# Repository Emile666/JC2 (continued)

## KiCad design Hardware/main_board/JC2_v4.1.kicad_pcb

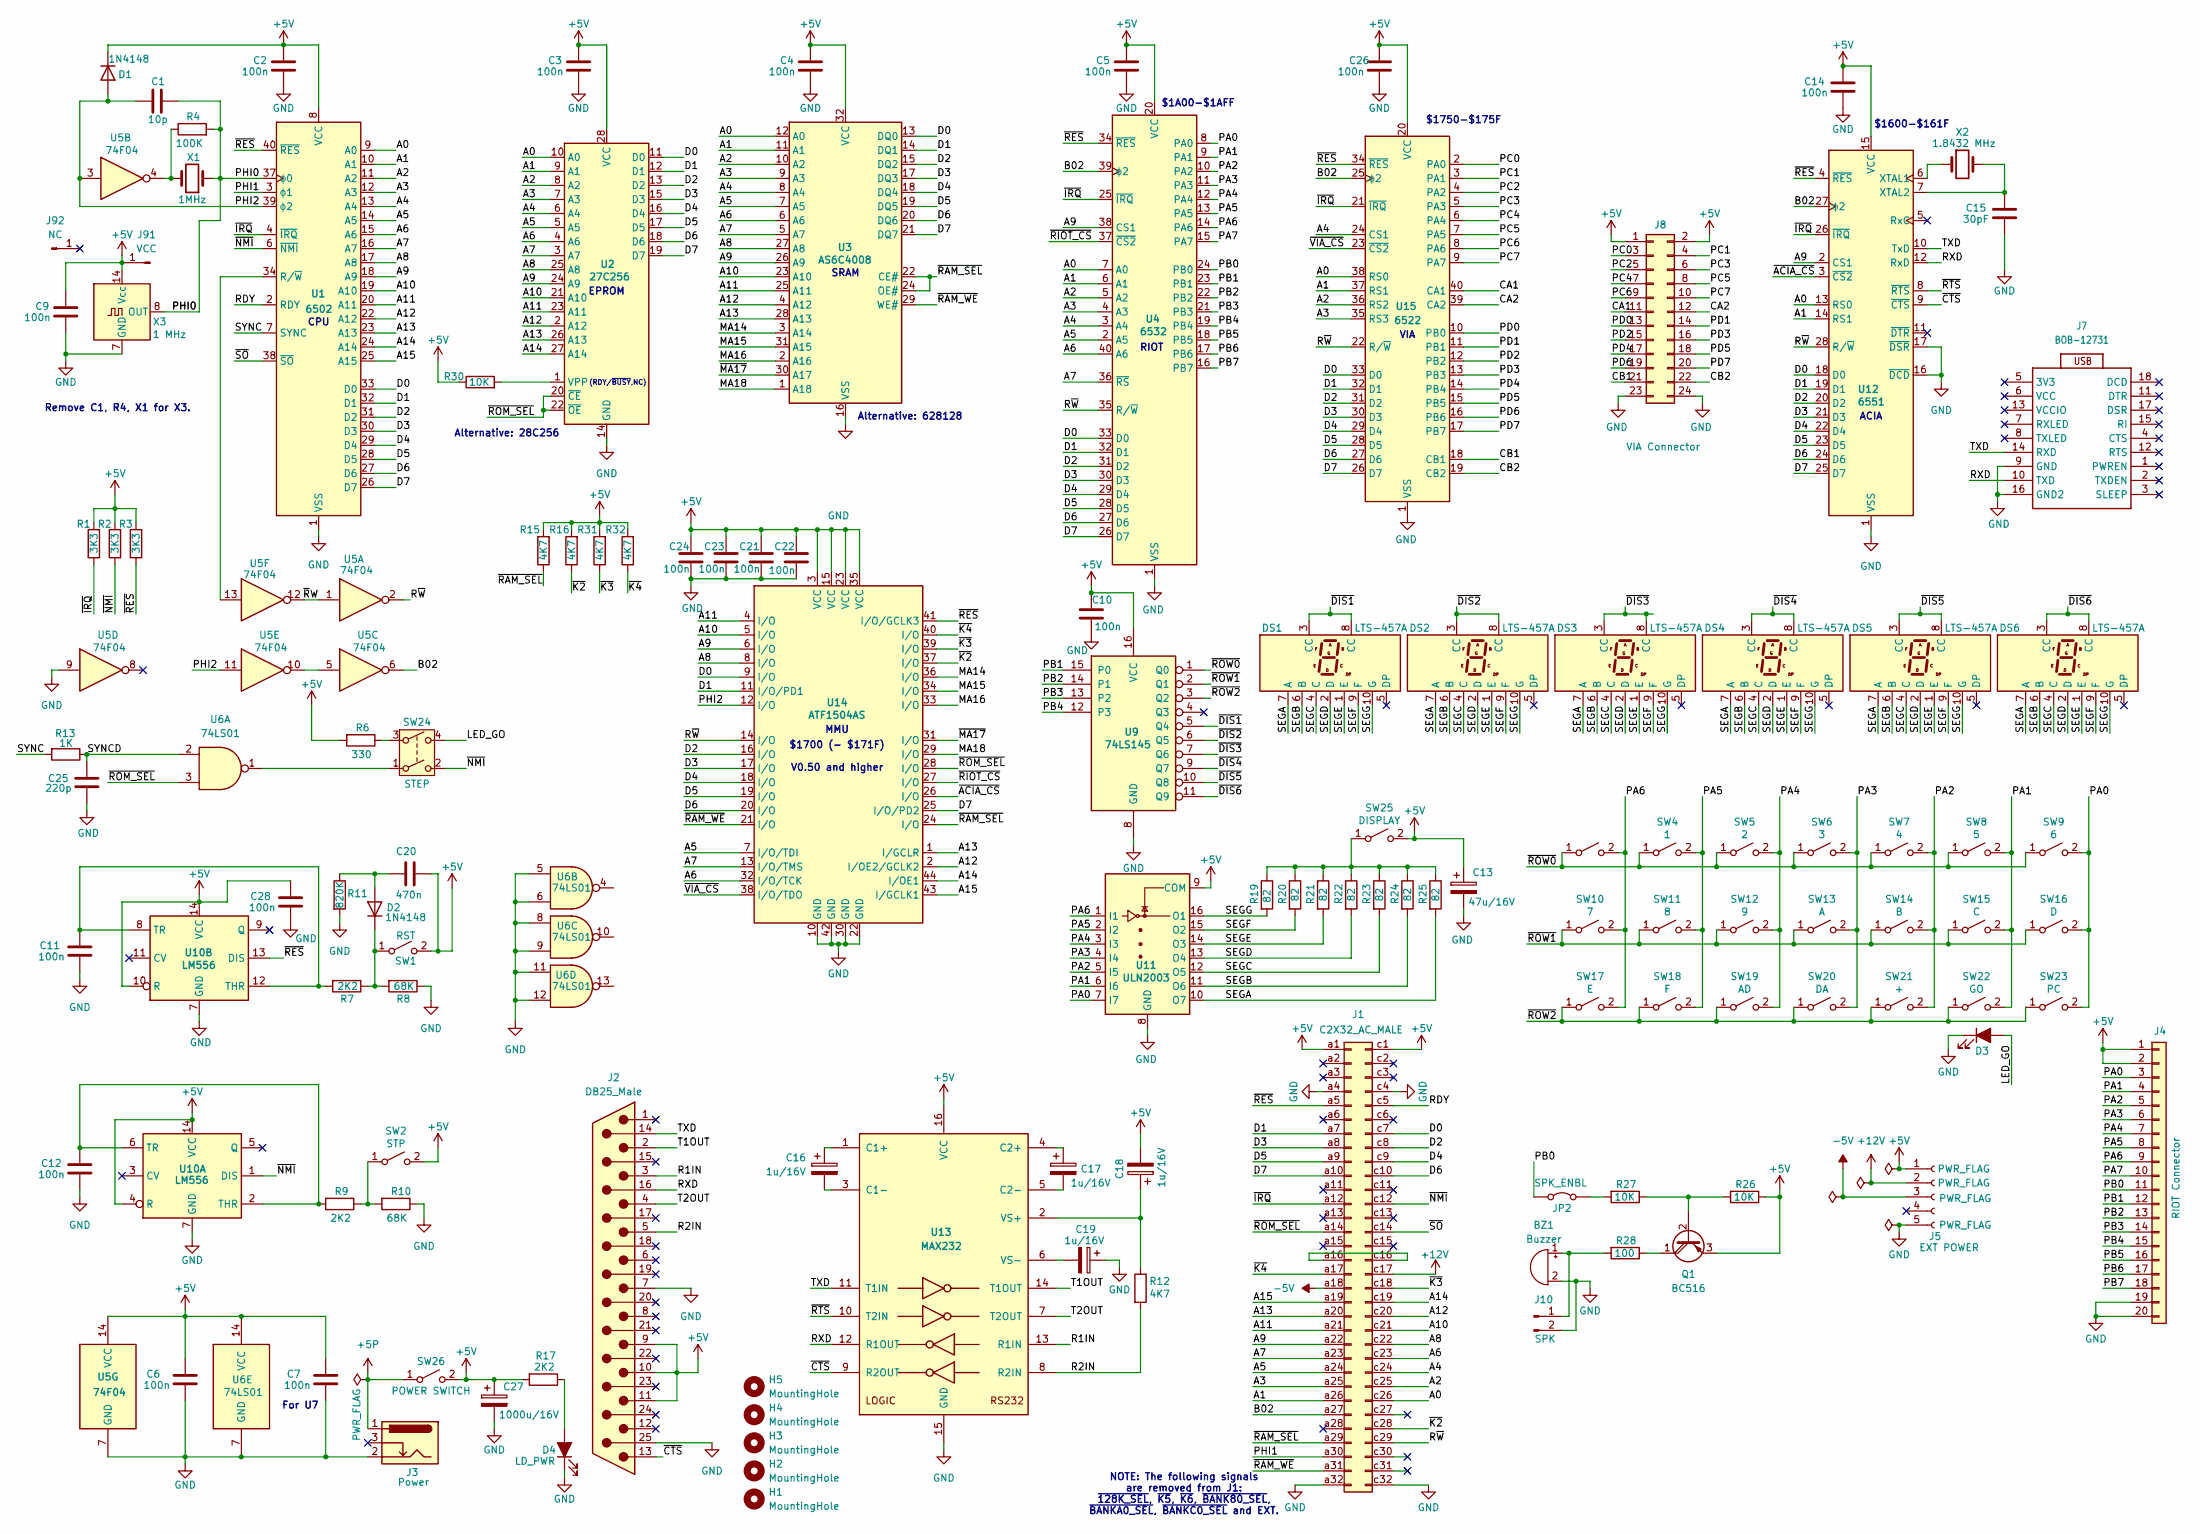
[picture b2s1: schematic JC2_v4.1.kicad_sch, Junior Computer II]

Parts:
BZ1: Buzzer; Buzzer_12x9.5RM7.6
C1: 10p; C_Rect_L4.6mm_W2.0mm_P2.50mm_MKS02_FKP02
C2, C3, C4, C5, C6, C7, C9, C10, C11, C12, C14, C26, C28: 100n; C_Rect_L4.6mm_W2.0mm_P2.50mm_MKS02_FKP02
C13: 47u/16V; CP_Radial_D5.0mm_P2.00mm
C15: 30pF; C_Rect_L4.6mm_W2.0mm_P2.50mm_MKS02_FKP02
C16, C17, C18, C19: 1u/16V; CP_Radial_D5.0mm_P2.00mm
C20: 470n; C_Rect_L4.6mm_W2.0mm_P2.50mm_MKS02_FKP02
C21, C22, C23, C24: 100n; C_1206_3216Metric_Pad1.33x1.80mm_HandSolder
C25: 220p; C_Rect_L4.6mm_W2.0mm_P2.50mm_MKS02_FKP02
C27: 1000u/16V; CP_Radial_D10.0mm_P5.00mm
D1, D2: 1N4148; D_DO-35_SOD27_P7.62mm_Horizontal
D3: LD_GO; LED_D3.0mm
D4: LD_PWR; LED_D3.0mm
DS1, DS2, DS3, DS4, DS5, DS6: LTS-457A
H1, H2, H3, H4, H5: MountingHole; MountingHole_4.3mm_M4
J1: C2X32_AC_MALE; DIN41612_C_2x32_Male_Horizontal_THT
J2: DB25_Male; DSUB-25_Male_Horizontal_P2.77x2.84mm_EdgePinOffset9.40mm
J3: Power; BarrelJack_GCT_DCJ200-10-A_Horizontal
J4: RIOT Connector; IDC-Header_2x10_P2.54mm_Vertical
J5: EXT POWER; PinHeader_1x05_P2.54mm_Vertical
J7: BOB-12731
J8: VIA Connector; IDC-Header_2x12_P2.54mm_Vertical
J10: SPK; PinHeader_1x02_P2.54mm_Vertical
J91: VCC; Pin_D0.9mm_L10.0mm_W2.4mm_FlatFork
J92: NC; Pin_D0.9mm_L10.0mm_W2.4mm_FlatFork
JP2: SPK_ENBL; PinHeader_1x02_P2.54mm_Vertical
Q1: BC516; TO-92_Inline
R1, R2, R3: 3K3; R_Axial_DIN0207_L6.3mm_D2.5mm_P10.16mm_Horizontal
R4: 100K; R_Axial_DIN0207_L6.3mm_D2.5mm_P10.16mm_Horizontal
R6: 330; R_Axial_DIN0207_L6.3mm_D2.5mm_P10.16mm_Horizontal
R7, R9, R17: 2K2; R_Axial_DIN0207_L6.3mm_D2.5mm_P10.16mm_Horizontal
R8, R10: 68K; R_Axial_DIN0207_L6.3mm_D2.5mm_P10.16mm_Horizontal
R11: 820K; R_Axial_DIN0207_L6.3mm_D2.5mm_P10.16mm_Horizontal
R12, R15, R16, R31, R32: 4K7; R_Axial_DIN0207_L6.3mm_D2.5mm_P10.16mm_Horizontal
R13: 1K; R_Axial_DIN0207_L6.3mm_D2.5mm_P10.16mm_Horizontal
R19, R20, R21, R22, R23, R24, R25: 82; R_Axial_DIN0207_L6.3mm_D2.5mm_P10.16mm_Horizontal
R26, R27, R30: 10K; R_Axial_DIN0207_L6.3mm_D2.5mm_P10.16mm_Horizontal
R28: 100; R_Axial_DIN0207_L6.3mm_D2.5mm_P10.16mm_Horizontal
SW1: RST; Switch_JC2
SW2: STP; Switch_JC2
SW3: 0; Switch_JC2
SW4: 1; Switch_JC2
SW5: 2; Switch_JC2
SW6: 3; Switch_JC2
SW7: 4; Switch_JC2
SW8: 5; Switch_JC2
SW9: 6; Switch_JC2
SW10: 7; Switch_JC2
SW11: 8; Switch_JC2
SW12: 9; Switch_JC2
SW13: A; Switch_JC2
SW14: B; Switch_JC2
SW15: C; Switch_JC2
SW16: D; Switch_JC2
SW17: E; Switch_JC2
SW18: F; Switch_JC2
SW19: AD; Switch_JC2
SW20: DA; Switch_JC2
SW21: +; Switch_JC2
SW22: GO; Switch_JC2
SW23: PC; Switch_JC2
SW24: STEP; SW_Push_2P2T_Toggle_CK_PVA2OAH5xxxxxxV2
SW25: DISPLAY; SW_Push_2P2T_Toggle_CK_PVA2OAH5xxxxxxV2
SW26: POWER SWITCH; SW_CK_JS202011CQN_DPDT_Straight
U1: 6502; DIP-40_W15.24mm
U2: 27C256; DIP-28_W15.24mm
U3: AS6C4008; DIP-32_W15.24mm
U4: 6532; DIP-40_W15.24mm
U5: 74F04; DIP-14_W7.62mm
U6: 74LS01; DIP-14_W7.62mm
U9: 74LS145; DIP-16_W7.62mm
U10: LM556; DIP-14_W7.62mm
U11: ULN2003; DIP-16_W7.62mm
U12: 6551; DIP-28_W15.24mm
U13: MAX232; DIP-16_W7.62mm
U14: ATF1504AS; PLCC-44_THT-Socket
U15: 6522; DIP-40_W15.24mm
X1: 1MHz; Crystal_HC18-U_Vertical
X2: 1.8432 MHz; Crystal_HC18-U_Horizontal
X3: 1 MHz; Oscillator_DIP-14

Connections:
+5P: J3.1, SW26.1 (A)
+5V: C2.1, C3.1, C4.1, C5.1, C6.1, C7.1, C9.1, C10.1, C13.1, C14.1, C18.2, C20.2, C21.1, C22.1, C23.1, C24.1, C26.1, C27.1, C28.1, D1.1 (K), J1.a1, J1.c1, J2.9, J2.10, J2.11, J4.1, J4.2, J5.1, J8.1, J8.2, J91.1, Q1.3 (E), R1.2, R2.2, R3.2, R6.2, R15.2, R16.2, R17.2, R26.1, R30.1, R31.2, R32.2, SW1.2 (B), SW2.2 (B), SW25.2 (B), SW26.2 (B), U1.8 (VCC), U2.28 (VCC), U3.32 (VCC), U4.20 (VCC), U5.14 (VCC), U6.14 (VCC), U9.16 (VCC), U10.4 (R), U10.10 (R), U10.14 (VCC), U11.9 (COM), U12.15 (VCC), U13.16 (VCC), U14.3 (VCC), U14.15 (VCC), U14.23 (VCC), U14.35 (VCC), U15.20 (VCC), X3.14 (Vcc)
+12V: J1.c17, J5.2
-5V: J1.a18, J5.3
/A0: J1.c26, U1.9 (A0), U2.10 (A0), U3.12 (A0), U4.7 (A0), U12.13 (RS0), U15.38 (RS0)
/A1: J1.a26, U1.10 (A1), U2.9 (A1), U3.11 (A1), U4.6 (A1), U12.14 (RS1), U15.37 (RS1)
/A2: J1.c25, U1.11 (A2), U2.8 (A2), U3.10 (A2), U4.5 (A2), U15.36 (RS2)
/A3: J1.a25, U1.12 (A3), U2.7 (A3), U3.9 (A3), U4.4 (A3), U15.35 (RS3)
/A4: J1.c24, U1.13 (A4), U2.6 (A4), U3.8 (A4), U4.3 (A4), U15.24 (CS1)
/A5: J1.a24, U1.14 (A5), U2.5 (A5), U3.7 (A5), U4.2 (A5), U14.7 (I/O/TDI)
/A6: J1.c23, U1.15 (A6), U2.4 (A6), U3.6 (A6), U4.40 (A6), U14.32 (I/O/TCK)
/A7: J1.a23, U1.16 (A7), U2.3 (A7), U3.5 (A7), U4.36 (~RS), U14.13 (I/O/TMS)
/A8: J1.c22, U1.17 (A8), U2.25 (A8), U3.27 (A8), U14.8 (I/O)
/A9: J1.a22, U1.18 (A9), U2.24 (A9), U3.26 (A9), U4.38 (CS1), U12.2 (CS1), U14.6 (I/O)
/A10: J1.c21, U1.19 (A10), U2.21 (A10), U3.23 (A10), U14.5 (I/O)
/A11: J1.a21, U1.20 (A11), U2.23 (A11), U3.25 (A11), U14.4 (I/O)
/A12: J1.c20, U1.22 (A12), U2.2 (A12), U3.4 (A12), U14.2 (I/OE2/GCLK2)
/A13: J1.a20, U1.23 (A13), U2.26 (A13), U3.28 (A13), U14.1 (I/GCLR)
/A14: J1.c19, U1.24 (A14), U2.27 (A14), U14.44 (I/OE1)
/A15: J1.a19, U1.25 (A15), U14.43 (I/GCLK1)
/B02: J1.a27, U4.39 (ϕ2), U5.6, U12.27 (ϕ2), U15.25 (ϕ2)
/CA1: J8.11, U15.40 (CA1)
/CA2: J8.12, U15.39 (CA2)
/CB1: J8.21, U15.18 (CB1)
/CB2: J8.22, U15.19 (CB2)
/D0: J1.c7, U1.33 (D0), U2.11 (D0), U3.13 (DQ0), U4.33 (D0), U12.18 (D0), U14.9 (I/O), U15.33 (D0)
/D1: J1.a7, U1.32 (D1), U2.12 (D1), U3.14 (DQ1), U4.32 (D1), U12.19 (D1), U14.11 (I/O/PD1), U15.32 (D1)
/D2: J1.c8, U1.31 (D2), U2.13 (D2), U3.15 (DQ2), U4.31 (D2), U12.20 (D2), U14.16 (I/O), U15.31 (D2)
/D3: J1.a8, U1.30 (D3), U2.15 (D3), U3.17 (DQ3), U4.30 (D3), U12.21 (D3), U14.17 (I/O), U15.30 (D3)
/D4: J1.c9, U1.29 (D4), U2.16 (D4), U3.18 (DQ4), U4.29 (D4), U12.22 (D4), U14.18 (I/O), U15.29 (D4)
/D5: J1.a9, U1.28 (D5), U2.17 (D5), U3.19 (DQ5), U4.28 (D5), U12.23 (D5), U14.19 (I/O), U15.28 (D5)
/D6: J1.c10, U1.27 (D6), U2.18 (D6), U3.20 (DQ6), U4.27 (D6), U12.24 (D6), U14.20 (I/O), U15.27 (D6)
/D7: J1.a10, U1.26 (D7), U2.19 (D7), U3.21 (DQ7), U4.26 (D7), U12.25 (D7), U14.25 (I/O/PD2), U15.26 (D7)
/LED_GO: D3.2 (A), SW24.4
/MA14: U3.3 (A14), U14.36 (I/O)
/MA15: U3.31 (A15), U14.34 (I/O)
/MA16: U3.2 (A16), U14.33 (I/O)
/MA18: U3.1 (A18), U14.29 (I/O)
/PA0: J4.3, SW9.2 (B), SW16.2 (B), SW23.2 (B), U4.8 (PA0), U11.7 (I7)
/PA1: J4.4, SW8.2 (B), SW15.2 (B), SW22.2 (B), U4.9 (PA1), U11.6 (I6)
/PA2: J4.5, SW7.2 (B), SW14.2 (B), SW21.2 (B), U4.10 (PA2), U11.5 (I5)
/PA3: J4.6, SW6.2 (B), SW13.2 (B), SW20.2 (B), U4.11 (PA3), U11.4 (I4)
/PA4: J4.7, SW5.2 (B), SW12.2 (B), SW19.2 (B), U4.12 (PA4), U11.3 (I3)
/PA5: J4.8, SW4.2 (B), SW11.2 (B), SW18.2 (B), U4.13 (PA5), U11.2 (I2)
/PA6: J4.9, SW3.2 (B), SW10.2 (B), SW17.2 (B), U4.14 (PA6), U11.1 (I1)
/PA7: J4.10, U4.15 (PA7)
/PB0: J4.11, JP2.1 (A), U4.24 (PB0)
/PB1: J4.12, U4.23 (PB1), U9.15 (P0)
/PB2: J4.13, U4.22 (PB2), U9.14 (P1)
/PB3: J4.14, U4.21 (PB3), U9.13 (P2)
/PB4: J4.15, U4.19 (PB4), U9.12 (P3)
/PB5: J4.16, U4.18 (PB5)
/PB6: J4.17, U4.17 (PB6)
/PB7: J4.18, U4.16 (PB7)
/PC0: J8.3, U15.2 (PA0)
/PC1: J8.4, U15.3 (PA1)
/PC2: J8.5, U15.4 (PA2)
/PC3: J8.6, U15.5 (PA3)
/PC4: J8.7, U15.6 (PA4)
/PC5: J8.8, U15.7 (PA5)
/PC6: J8.9, U15.8 (PA6)
/PC7: J8.10, U15.9 (PA7)
/PD0: J8.13, U15.10 (PB0)
/PD1: J8.14, U15.11 (PB1)
/PD2: J8.15, U15.12 (PB2)
/PD3: J8.16, U15.13 (PB3)
/PD4: J8.17, U15.14 (PB4)
/PD5: J8.18, U15.15 (PB5)
/PD6: J8.19, U15.16 (PB6)
/PD7: J8.20, U15.17 (PB7)
/PHI0: C1.2, R4.2, U1.37 (ϕ0), X1.1, X3.8 (OUT)
/PHI1: J1.a30, U1.3 (ϕ1)
/PHI2: C1.1, D1.2 (A), U1.39 (ϕ2), U5.3, U5.11, U14.12 (I/O)
/R1IN: J2.3, U13.13 (R1IN)
/R2IN: J2.5, R12.2, U13.8 (R2IN)
/RDY: J1.c5, U1.2 (RDY)
/RXD: J2.16, J7.10 (TXD), U12.12 (RxD), U13.12 (R1OUT)
/R~W: J1.c29, U4.35 (R/~W), U5.2, U12.28 (R/~W), U14.14 (I/O), U15.22 (R/~W)
/SEGA: DS1.7 (A), DS2.7 (A), DS3.7 (A), DS4.7 (A), DS5.7 (A), DS6.7 (A), R25.2, U11.10 (O7)
/SEGB: DS1.6 (B), DS2.6 (B), DS3.6 (B), DS4.6 (B), DS5.6 (B), DS6.6 (B), R24.2, U11.11 (O6)
/SEGC: DS1.4 (C), DS2.4 (C), DS3.4 (C), DS4.4 (C), DS5.4 (C), DS6.4 (C), R23.2, U11.12 (O5)
/SEGD: DS1.2 (D), DS2.2 (D), DS3.2 (D), DS4.2 (D), DS5.2 (D), DS6.2 (D), R22.2, U11.13 (O4)
/SEGE: DS1.1 (E), DS2.1 (E), DS3.1 (E), DS4.1 (E), DS5.1 (E), DS6.1 (E), R21.2, U11.14 (O3)
/SEGF: DS1.9 (F), DS2.9 (F), DS3.9 (F), DS4.9 (F), DS5.9 (F), DS6.9 (F), R20.2, U11.15 (O2)
/SEGG: DS1.10 (G), DS2.10 (G), DS3.10 (G), DS4.10 (G), DS5.10 (G), DS6.10 (G), R19.2, U11.16 (O1)
/SYNC: R13.2, U1.7 (SYNC)
/SYNCD: C25.1, R13.1, U6.2
/T1OUT: J2.2, U13.14 (T1OUT)
/T2OUT: J2.4, U13.7 (T2OUT)
/TXD: J2.14, J7.14 (RXD), U12.10 (TxD), U13.11 (T1IN)
/~ACIA_CS: U12.3 (~CS2), U14.26 (I/O)
/~CTS: J2.13, U12.9 (~CTS), U13.9 (R2OUT)
/~DIS1: DS1.3 (CC), DS1.8 (CC), U9.5 (Q4)
/~DIS2: DS2.3 (CC), DS2.8 (CC), U9.6 (Q5)
/~DIS3: DS3.3 (CC), DS3.8 (CC), U9.7 (Q6)
/~DIS4: DS4.3 (CC), DS4.8 (CC), U9.9 (Q7)
/~DIS5: DS5.3 (CC), DS5.8 (CC), U9.10 (Q8)
/~DIS6: DS6.3 (CC), DS6.8 (CC), U9.11 (Q9)
/~IRQ: J1.a12, R1.1, U1.4 (~IRQ), U4.25 (~IRQ), U12.26 (~IRQ), U15.21 (~IRQ)
/~K2: J1.c28, R16.1, U14.37 (I/O)
/~K3: J1.c18, R31.1, U14.39 (I/O)
/~K4: J1.a17, R32.1, U14.40 (I/O)
/~MA17: U3.30 (A17), U14.31 (I/O)
/~NMI: J1.c12, R2.1, SW24.2, U1.6 (~NMI), U10.1 (DIS)
/~RAM_SEL: J1.a29, R15.1, U3.22 (CE#), U3.24 (OE#), U14.24 (I/O)
/~RAM_WE: J1.a31, U3.29 (WE#), U14.21 (I/O)
/~RES: J1.a5, R3.1, U1.40 (~RES), U4.34 (~RES), U10.13 (DIS), U12.4 (~RES), U14.41 (I/O/GCLK3), U15.34 (~RES)
/~RIOT_CS: U4.37 (~CS2), U14.27 (I/O)
/~ROM_SEL: J1.a14, U2.20 (~CE), U2.22 (~OE), U6.3, U14.28 (I/O)
/~ROW0: SW3.1 (A), SW4.1 (A), SW5.1 (A), SW6.1 (A), SW7.1 (A), SW8.1 (A), SW9.1 (A), U9.1 (Q0)
/~ROW1: SW10.1 (A), SW11.1 (A), SW12.1 (A), SW13.1 (A), SW14.1 (A), SW15.1 (A), SW16.1 (A), U9.2 (Q1)
/~ROW2: SW17.1 (A), SW18.1 (A), SW19.1 (A), SW20.1 (A), SW21.1 (A), SW22.1 (A), SW23.1 (A), U9.3 (Q2)
/~RTS: U12.8 (~RTS), U13.10 (T2IN)
/~RW: U5.1, U5.12
/~SO: J1.c14, U1.38 (~SO)
/~VIA_CS: U14.38 (I/O/TDO), U15.23 (~CS2)
GND: BZ1.2 (-), C2.2, C3.2, C4.2, C5.2, C6.2, C7.2, C9.2, C10.2, C11.2, C12.2, C13.2, C14.2, C15.2, C19.1, C21.2, C22.2, C23.2, C24.2, C25.2, C26.2, C27.2, C28.2, D3.1 (K), D4.1 (K), J1.a4, J1.a32, J1.c4, J1.c32, J2.7, J2.25, J3.2, J4.19, J4.20, J5.5, J7.9 (GND), J7.16 (GND2), J8.23, J8.24, J10.2, R8.1, R10.1, R11.2, U1.1 (VSS), U1.21 (VSS), U2.14 (GND), U3.16 (VSS), U4.1 (VSS), U5.7 (GND), U5.9, U6.5, U6.6, U6.7 (GND), U6.8, U6.9, U6.11, U6.12, U9.8 (GND), U10.7 (GND), U11.8 (GND), U12.1 (VSS), U12.16 (~DCD), U12.17 (~DSR), U13.15 (GND), U14.10 (GND), U14.22 (GND), U14.30 (GND), U14.42 (GND), U15.1 (VSS), X3.7 (GND)
unnamed: BZ1.1 (+), J10.1, R28.2
unnamed: C20.1, D2.2 (A), R11.1
unnamed: D2.1 (K), R7.1, R8.2, SW1.1 (A)
unnamed: D4.2 (A), R17.1
unnamed: J1.a16, J1.c16
unnamed: JP2.2 (B), R27.2
unnamed: Q1.2 (B), R26.2, R27.1
unnamed: Q1.1 (C), R28.1
unnamed: R4.1, U5.4, X1.2
unnamed: R6.1, SW24.3
unnamed: R9.1, R10.2, SW2.1 (A)
unnamed: SW24.1, U6.1
unnamed: R19.1, R20.1, R21.1, R22.1, R23.1, R24.1, R25.1, SW25.1 (A)
unnamed: U1.34 (R/~W), U5.13
unnamed: R30.2, U2.1 (VPP)
unnamed: U5.5, U5.10
unnamed: C12.1, R9.2, U10.2 (THR), U10.6 (TR)
unnamed: C11.1, R7.2, U10.8 (TR), U10.12 (THR)
unnamed: U12.6 (XTAL1), X2.1
unnamed: C15.1, U12.7 (XTAL2), X2.2
unnamed: C16.1, U13.1 (C1+)
unnamed: C16.2, U13.3 (C1-)
unnamed: C17.1, U13.4 (C2+)
unnamed: C17.2, U13.5 (C2-)
unnamed: C18.1, R12.1, U13.2 (VS+)
unnamed: C19.2, U13.6 (VS-)

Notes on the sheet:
$1A00-$1AFF
VIA
Alternative: 28C256
$1700 (- $171F) V0.50 and higher
For U7
Alternative: 628128
ACIA
RIOT
(RDY/~{BUSY},NC)
EPROM
CPU
SRAM
NOTE: The following signals are removed from J1: ~{128K_SEL}, ~{K5}, ~{K6}, ~{BANK80_SEL}, ~{BANKA0_SEL}, ~{BANKC0_SEL} and EXT.
$1600-$161F
MMU
$1750-$175F
Remove C1, R4, X1 for X3.

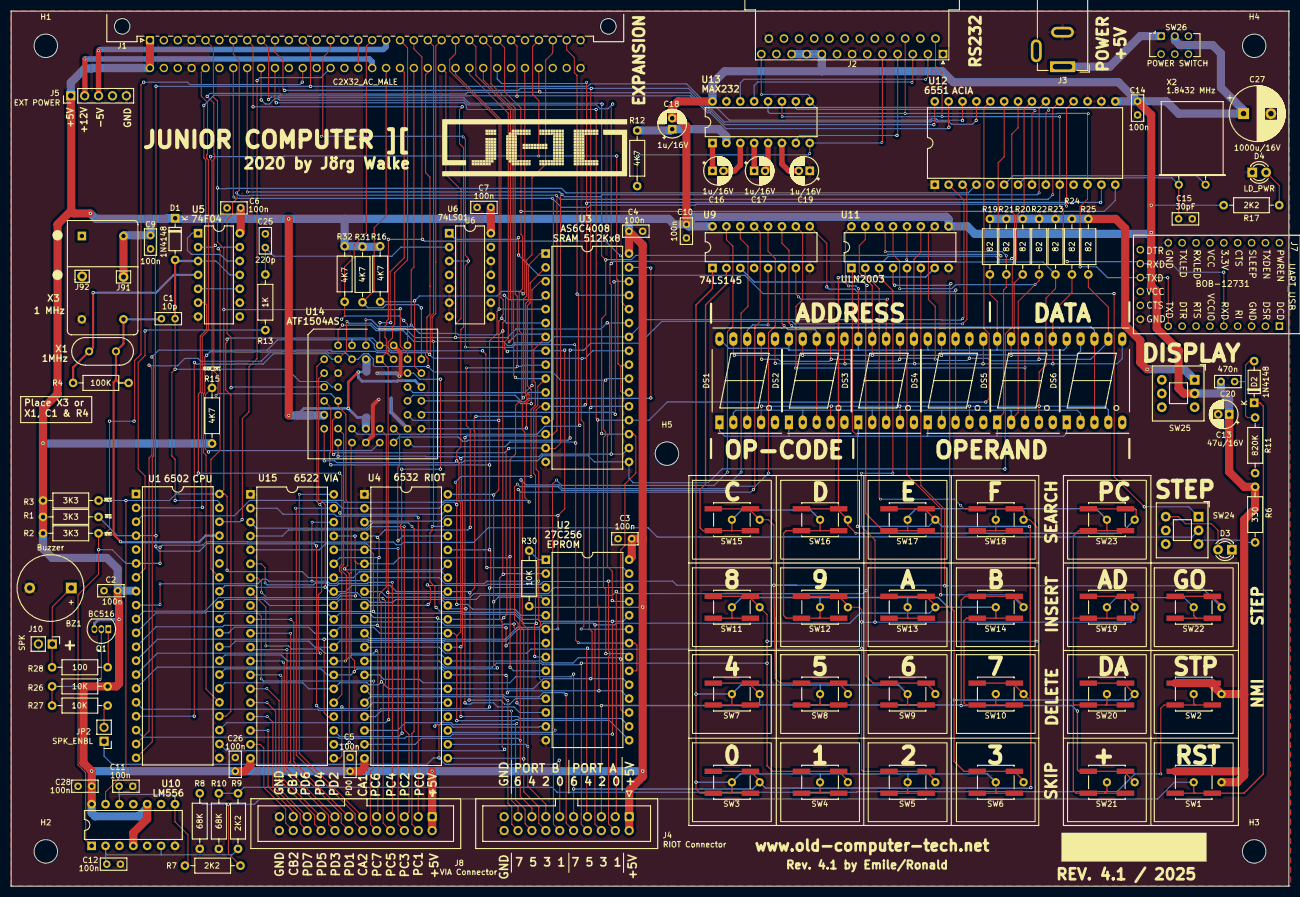
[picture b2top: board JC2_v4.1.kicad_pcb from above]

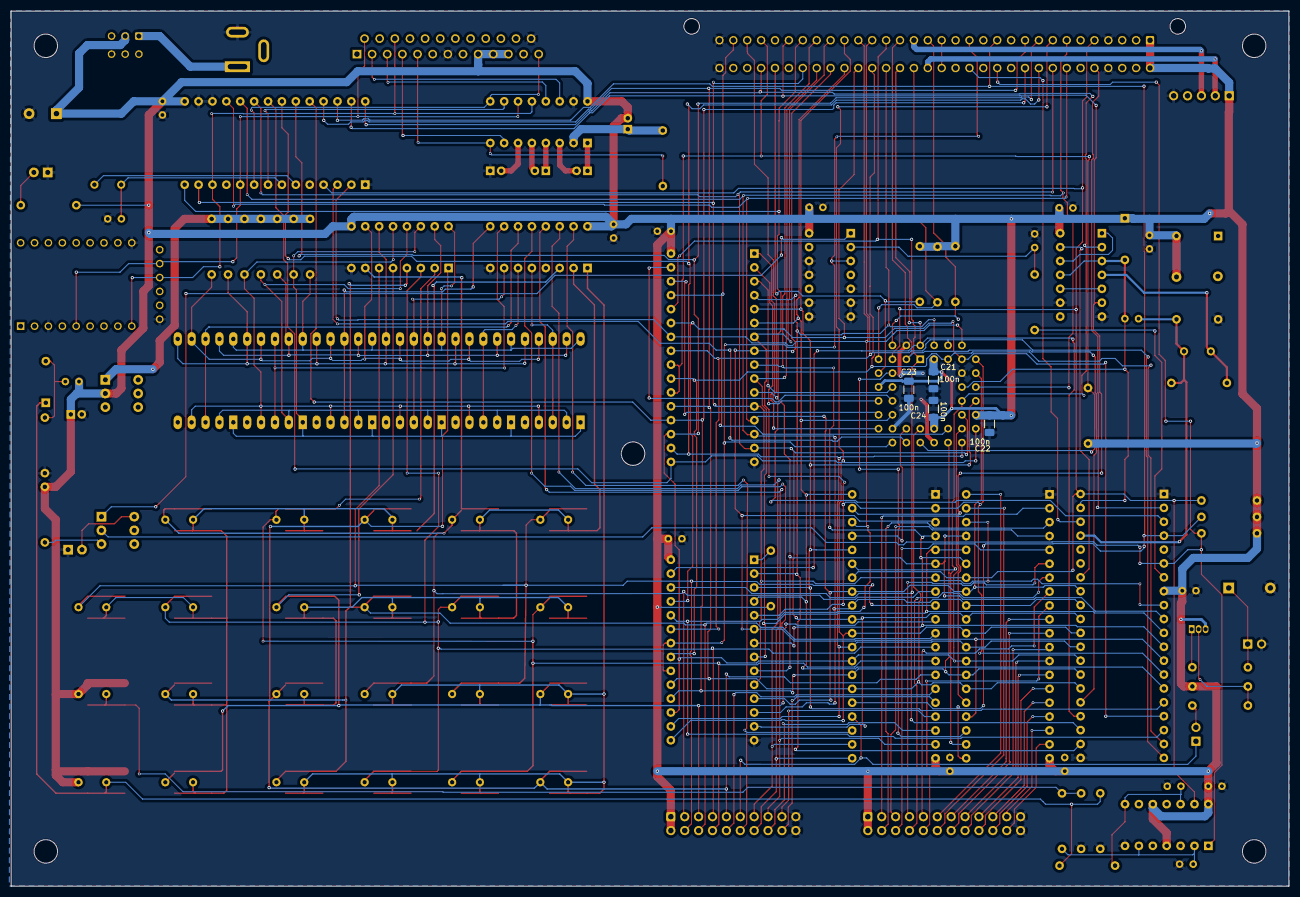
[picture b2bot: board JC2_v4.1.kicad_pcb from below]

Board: 2 copper layers, 233.7 x 160.0 mm, 125 parts (4 on the bottom side), 143 nets.

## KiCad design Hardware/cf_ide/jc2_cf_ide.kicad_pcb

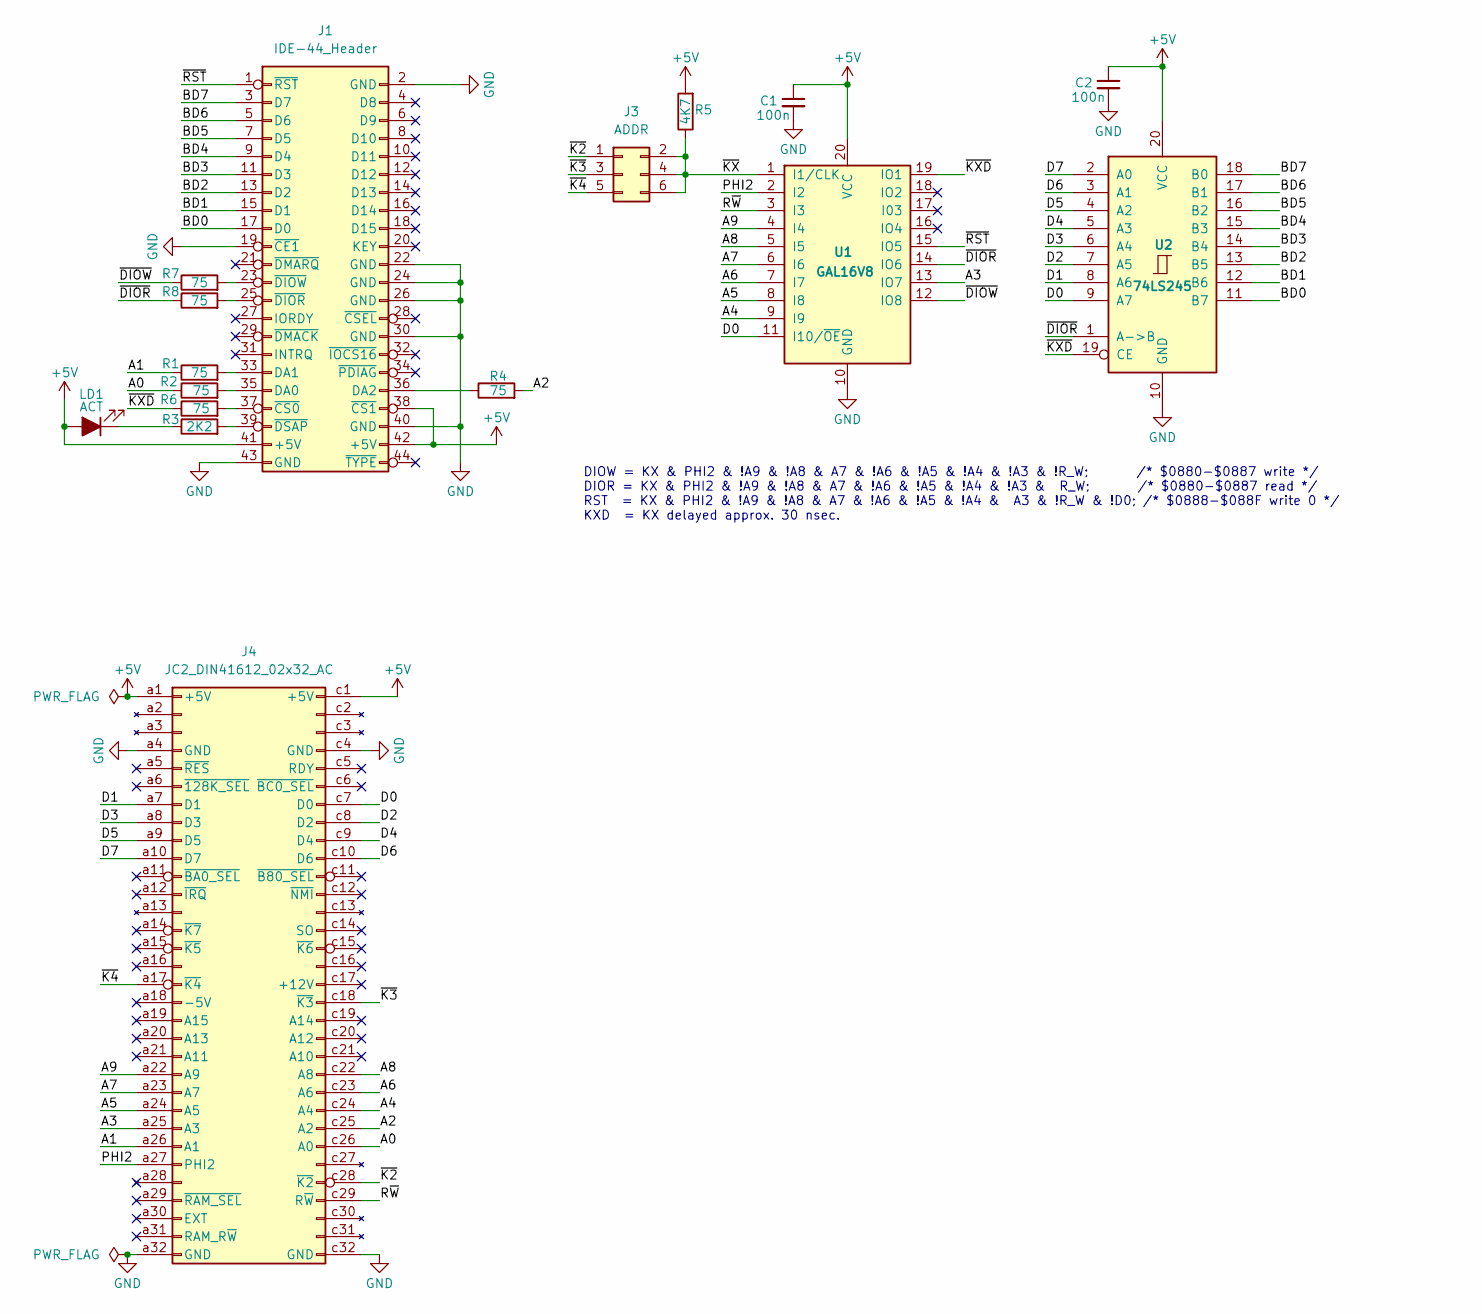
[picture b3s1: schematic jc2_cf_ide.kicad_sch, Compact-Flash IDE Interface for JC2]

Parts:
C1, C2: 100n; C_1206_3216Metric_Pad1.33x1.80mm_HandSolder
J1: IDE-44_Header; PinHeader_2x22_P2.00mm_Vertical
J3: ADDR; PinHeader_2x03_P2.00mm_Vertical
J4: JC2_DIN41612_02x32_AC; DIN41612_C_2x32_Male_Horizontal_THT
LD1: ACT; LED_1206_3216Metric_Pad1.42x1.75mm_HandSolder
R1, R2, R4, R6, R7, R8: 75; R_1206_3216Metric_Pad1.30x1.75mm_HandSolder
R3: 2K2; R_1206_3216Metric_Pad1.30x1.75mm_HandSolder
R5: 4K7; R_1206_3216Metric_Pad1.30x1.75mm_HandSolder
U1: GAL16V8; DIP-20_W7.62mm
U2: 74LS245; DIP-20_W7.62mm

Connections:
+5V: C1.1, C2.1, J1.38 (~CS1), J1.41 (+5V), J1.42 (+5V), J4.a1 (+5V), J4.c1 (+5V), LD1.2 (A), R5.2, U1.20 (VCC), U2.20 (VCC)
/A0: J4.c26 (A0), R2.1
/A1: J4.a26 (A1), R1.1
/A2: J4.c25 (A2), R4.2
/A3: J4.a25 (A3), U1.13 (IO7)
/A4: J4.c24 (A4), U1.9 (I9)
/A5: J4.a24 (A5), U1.8 (I8)
/A6: J4.c23 (A6), U1.7 (I7)
/A7: J4.a23 (A7), U1.6 (I6)
/A8: J4.c22 (A8), U1.5 (I5)
/A9: J4.a22 (A9), U1.4 (I4)
/BD0: J1.17 (D0), U2.11 (B7)
/BD1: J1.15 (D1), U2.12 (B6)
/BD2: J1.13 (D2), U2.13 (B5)
/BD3: J1.11 (D3), U2.14 (B4)
/BD4: J1.9 (D4), U2.15 (B3)
/BD5: J1.7 (D5), U2.16 (B2)
/BD6: J1.5 (D6), U2.17 (B1)
/BD7: J1.3 (D7), U2.18 (B0)
/D0: J4.c7 (D0), U1.11 (I10/~OE), U2.9 (A7)
/D1: J4.a7 (D1), U2.8 (A6)
/D2: J4.c8 (D2), U2.7 (A5)
/D3: J4.a8 (D3), U2.6 (A4)
/D4: J4.c9 (D4), U2.5 (A3)
/D5: J4.a9 (D5), U2.4 (A2)
/D6: J4.c10 (D6), U2.3 (A1)
/D7: J4.a10 (D7), U2.2 (A0)
/PHI2: J4.a27 (PHI2), U1.2 (I2)
/R~W: J4.c29 (R~W), U1.3 (I3)
/~DIOR: R8.1, U1.14 (IO6), U2.1 (A->B)
/~DIOW: R7.1, U1.12 (IO8)
/~K2: J3.1, J4.c28 (~K2)
/~K3: J3.3, J4.c18 (~K3)
/~K4: J3.5, J4.a17 (~K4)
/~KXD: R6.1, U1.19 (IO1), U2.19 (CE)
/~KX: J3.2, J3.4, J3.6, R5.1, U1.1 (I1/CLK)
/~RST: J1.1 (~RST), U1.15 (IO5)
GND: C1.2, C2.2, J1.2 (GND), J1.19 (~CE1), J1.22 (GND), J1.24 (GND), J1.26 (GND), J1.30 (GND), J1.40 (GND), J1.43 (GND), J4.a4 (GND), J4.a32 (GND), J4.c4 (GND), J4.c32 (GND), U1.10 (GND), U2.10 (GND)
unnamed: J1.35 (DA0), R2.2
unnamed: J1.33 (DA1), R1.2
unnamed: J1.36 (DA2), R4.1
unnamed: J1.37 (~CS0), R6.2
unnamed: J1.25 (~DIOR), R8.2
unnamed: J1.23 (~DIOW), R7.2
unnamed: J1.39 (~DSAP), R3.2
unnamed: LD1.1 (K), R3.1

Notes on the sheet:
DIOW = KX & PHI2 & !A9 & !A8 & A7 & !A6 & !A5 & !A4 & !A3 & !R_W; /* $0880-$0887 write */ DIOR = KX & PHI2 & !A9 & !A8 & A7 & !A6 & !A5 & !A4 & !A3 & R_W; /* $0880-$0887 read */ RST = KX & PHI2 & !A9 & !A8 & A7 & !A6 & !A5 & !A4 & A3 & !R_W & !D0; /* $0888-$088F write 0 */ KXD = KX delayed approx. 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

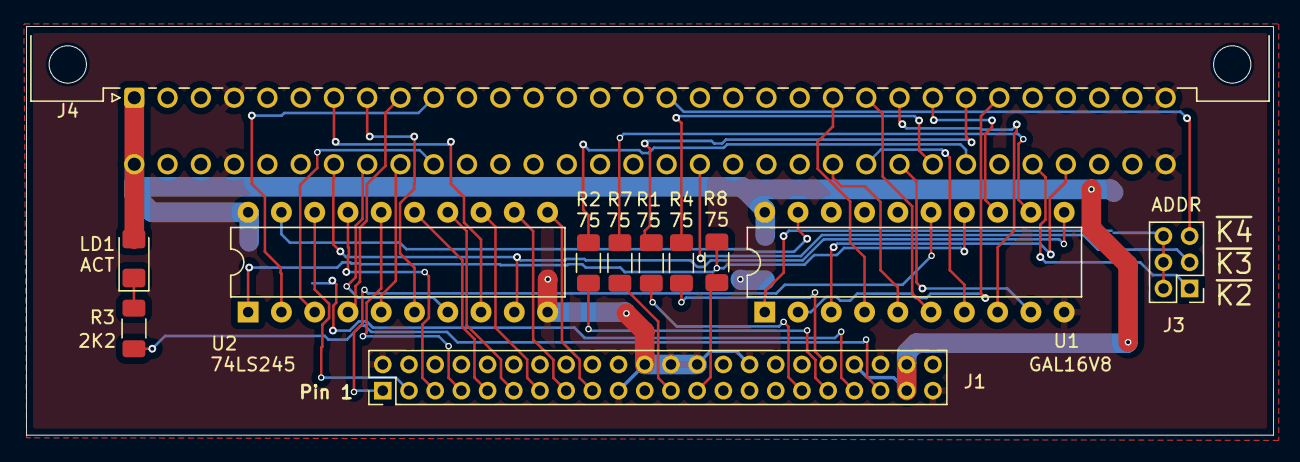
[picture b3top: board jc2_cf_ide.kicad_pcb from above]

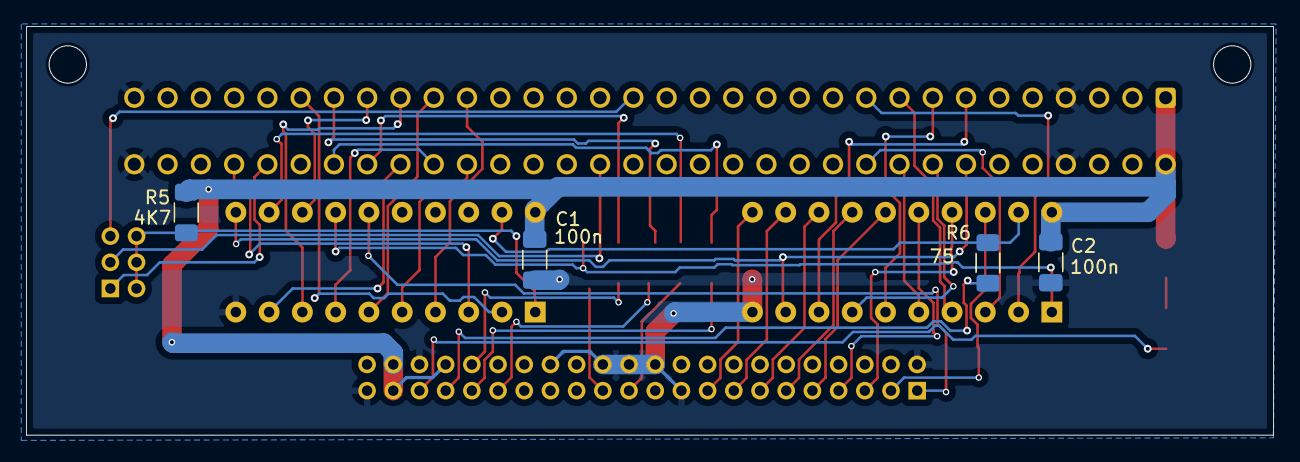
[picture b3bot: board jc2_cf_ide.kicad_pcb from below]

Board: 2 copper layers, 95.2 x 31.2 mm, 16 parts (4 on the bottom side), 46 nets.

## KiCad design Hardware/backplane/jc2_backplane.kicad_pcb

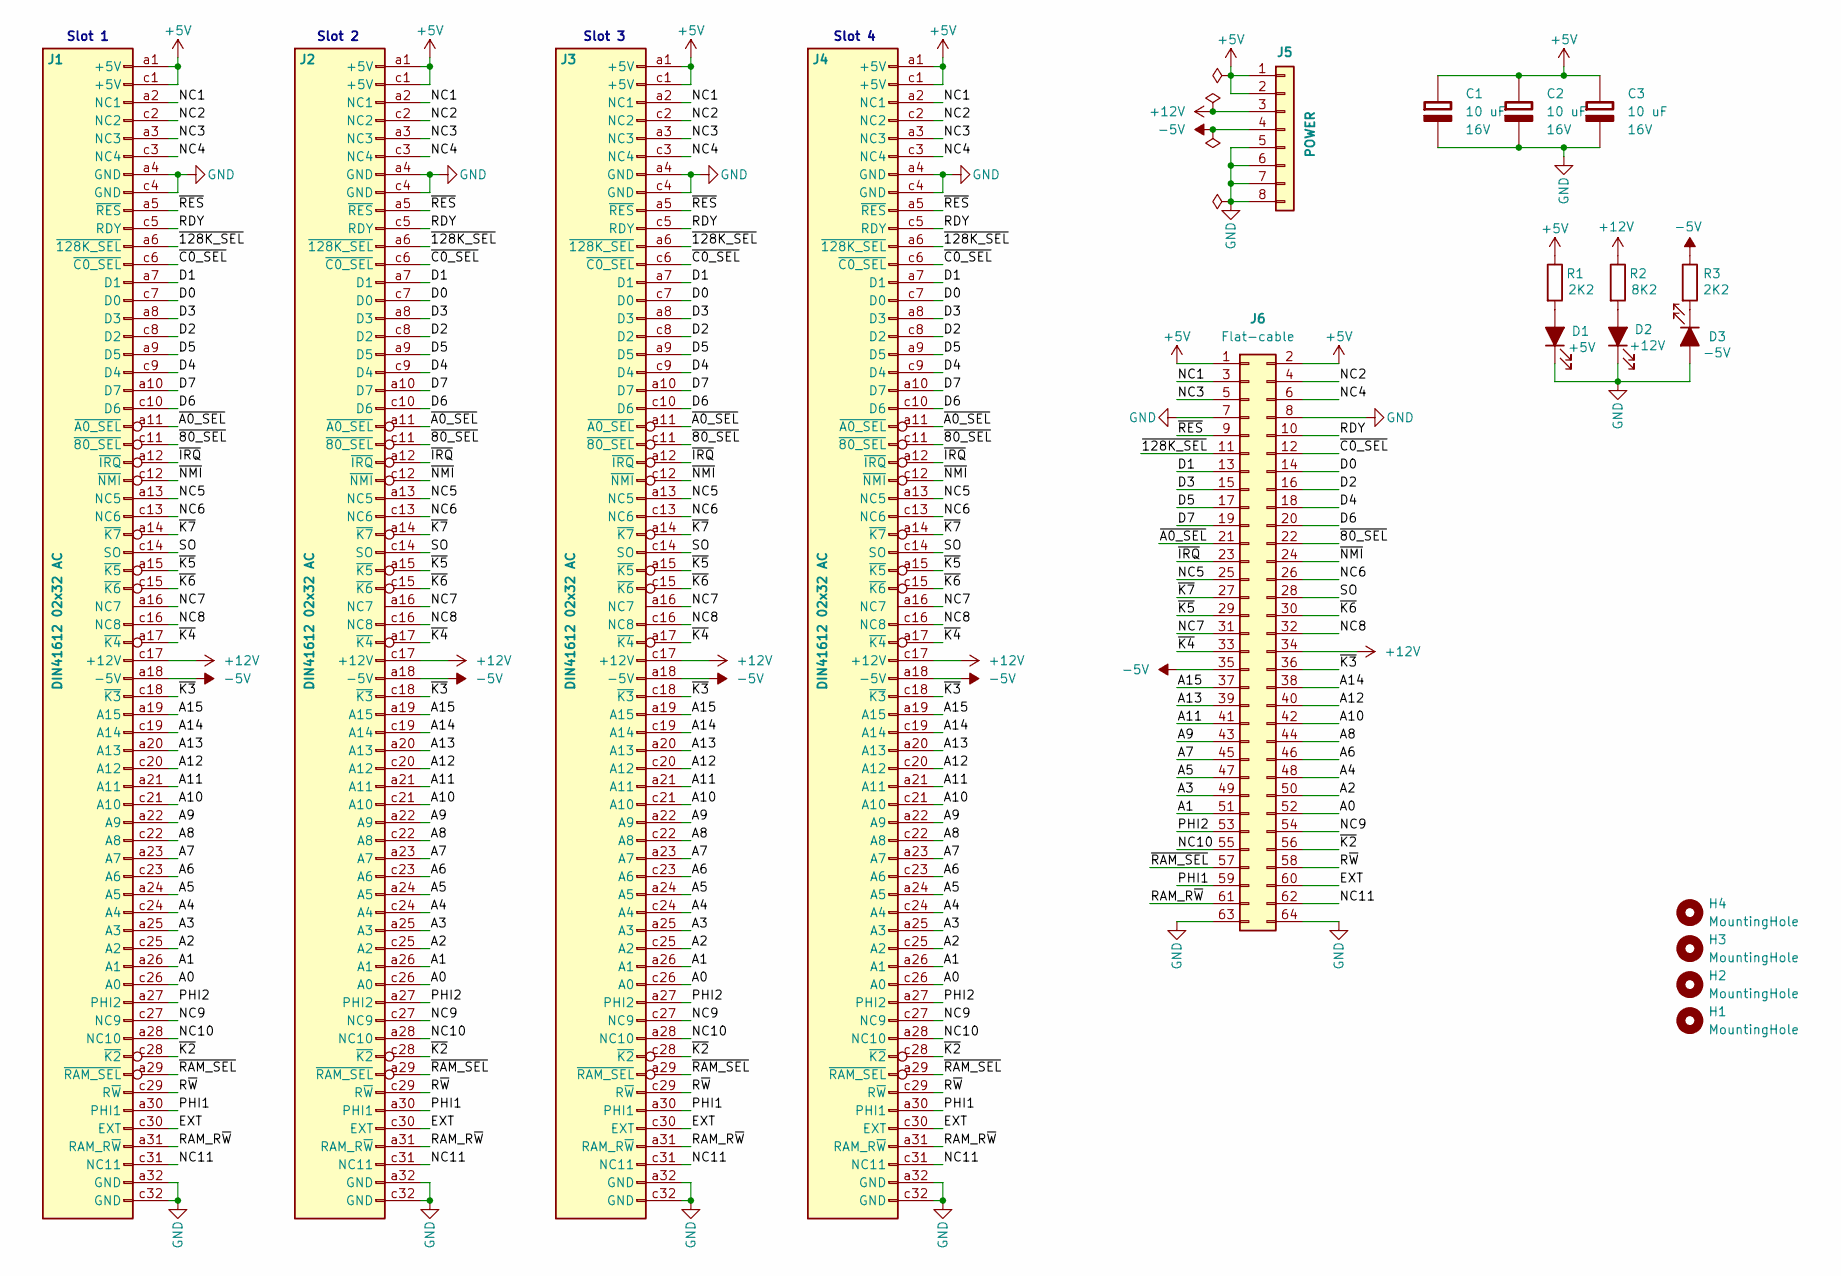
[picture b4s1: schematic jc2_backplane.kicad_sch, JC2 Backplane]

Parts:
C1, C2, C3: 10 uF; CP_Radial_D5.0mm_P2.00mm; Rating 16V
D1: +5V; LED_1206_3216Metric_Pad1.42x1.75mm_HandSolder
D2: +12V; LED_1206_3216Metric_Pad1.42x1.75mm_HandSolder
D3: -5V; LED_1206_3216Metric_Pad1.42x1.75mm_HandSolder
H1, H2, H3, H4: MountingHole; MountingHole_3.2mm_M3
J1, J2, J3, J4: DIN41612 02x32 AC; DIN41612_C_2x32_Female_Vertical_THT
J5: POWER; Molex_Mini-Fit_Jr_5566-08A_2x04_P4.20mm_Vertical
J6: Flat-cable; IDC-Header_2x32_P2.54mm_Horizontal
R1, R3: 2K2; R_1206_3216Metric_Pad1.30x1.75mm_HandSolder
R2: 8K2; R_1206_3216Metric_Pad1.30x1.75mm_HandSolder

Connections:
+5V: C1.1 (+), C2.1 (+), C3.1 (+), J1.a1 (+5V), J1.c1 (+5V), J2.a1 (+5V), J2.c1 (+5V), J3.a1 (+5V), J3.c1 (+5V), J4.a1 (+5V), J4.c1 (+5V), J5.1, J5.2, J6.1, J6.2, R1.1
+12V: J1.c17 (+12V), J2.c17 (+12V), J3.c17 (+12V), J4.c17 (+12V), J5.3, J6.34, R2.1
-5V: J1.a18 (-5V), J2.a18 (-5V), J3.a18 (-5V), J4.a18 (-5V), J5.4, J6.35, R3.1
/A0: J1.c26 (A0), J2.c26 (A0), J3.c26 (A0), J4.c26 (A0), J6.52
/A1: J1.a26 (A1), J2.a26 (A1), J3.a26 (A1), J4.a26 (A1), J6.51
/A2: J1.c25 (A2), J2.c25 (A2), J3.c25 (A2), J4.c25 (A2), J6.50
/A3: J1.a25 (A3), J2.a25 (A3), J3.a25 (A3), J4.a25 (A3), J6.49
/A4: J1.c24 (A4), J2.c24 (A4), J3.c24 (A4), J4.c24 (A4), J6.48
/A5: J1.a24 (A5), J2.a24 (A5), J3.a24 (A5), J4.a24 (A5), J6.47
/A6: J1.c23 (A6), J2.c23 (A6), J3.c23 (A6), J4.c23 (A6), J6.46
/A7: J1.a23 (A7), J2.a23 (A7), J3.a23 (A7), J4.a23 (A7), J6.45
/A8: J1.c22 (A8), J2.c22 (A8), J3.c22 (A8), J4.c22 (A8), J6.44
/A9: J1.a22 (A9), J2.a22 (A9), J3.a22 (A9), J4.a22 (A9), J6.43
/A10: J1.c21 (A10), J2.c21 (A10), J3.c21 (A10), J4.c21 (A10), J6.42
/A11: J1.a21 (A11), J2.a21 (A11), J3.a21 (A11), J4.a21 (A11), J6.41
/A12: J1.c20 (A12), J2.c20 (A12), J3.c20 (A12), J4.c20 (A12), J6.40
/A13: J1.a20 (A13), J2.a20 (A13), J3.a20 (A13), J4.a20 (A13), J6.39
/A14: J1.c19 (A14), J2.c19 (A14), J3.c19 (A14), J4.c19 (A14), J6.38
/A15: J1.a19 (A15), J2.a19 (A15), J3.a19 (A15), J4.a19 (A15), J6.37
/D0: J1.c7 (D0), J2.c7 (D0), J3.c7 (D0), J4.c7 (D0), J6.14
/D1: J1.a7 (D1), J2.a7 (D1), J3.a7 (D1), J4.a7 (D1), J6.13
/D2: J1.c8 (D2), J2.c8 (D2), J3.c8 (D2), J4.c8 (D2), J6.16
/D3: J1.a8 (D3), J2.a8 (D3), J3.a8 (D3), J4.a8 (D3), J6.15
/D4: J1.c9 (D4), J2.c9 (D4), J3.c9 (D4), J4.c9 (D4), J6.18
/D5: J1.a9 (D5), J2.a9 (D5), J3.a9 (D5), J4.a9 (D5), J6.17
/D6: J1.c10 (D6), J2.c10 (D6), J3.c10 (D6), J4.c10 (D6), J6.20
/D7: J1.a10 (D7), J2.a10 (D7), J3.a10 (D7), J4.a10 (D7), J6.19
/EXT: J1.c30 (EXT), J2.c30 (EXT), J3.c30 (EXT), J4.c30 (EXT), J6.60
/NC1: J1.a2 (NC1), J2.a2 (NC1), J3.a2 (NC1), J4.a2 (NC1), J6.3
/NC2: J1.c2 (NC2), J2.c2 (NC2), J3.c2 (NC2), J4.c2 (NC2), J6.4
/NC3: J1.a3 (NC3), J2.a3 (NC3), J3.a3 (NC3), J4.a3 (NC3), J6.5
/NC4: J1.c3 (NC4), J2.c3 (NC4), J3.c3 (NC4), J4.c3 (NC4), J6.6
/NC5: J1.a13 (NC5), J2.a13 (NC5), J3.a13 (NC5), J4.a13 (NC5), J6.25
/NC6: J1.c13 (NC6), J2.c13 (NC6), J3.c13 (NC6), J4.c13 (NC6), J6.26
/NC7: J1.a16 (NC7), J2.a16 (NC7), J3.a16 (NC7), J4.a16 (NC7), J6.31
/NC8: J1.c16 (NC8), J2.c16 (NC8), J3.c16 (NC8), J4.c16 (NC8), J6.32
/NC9: J1.c27 (NC9), J2.c27 (NC9), J3.c27 (NC9), J4.c27 (NC9), J6.54
/NC10: J1.a28 (NC10), J2.a28 (NC10), J3.a28 (NC10), J4.a28 (NC10), J6.55
/NC11: J1.c31 (NC11), J2.c31 (NC11), J3.c31 (NC11), J4.c31 (NC11), J6.62
/PHI1: J1.a30 (PHI1), J2.a30 (PHI1), J3.a30 (PHI1), J4.a30 (PHI1), J6.59
/PHI2: J1.a27 (PHI2), J2.a27 (PHI2), J3.a27 (PHI2), J4.a27 (PHI2), J6.53
/RAM_R~W: J1.a31 (RAM_R~W), J2.a31 (RAM_R~W), J3.a31 (RAM_R~W), J4.a31 (RAM_R~W), J6.61
/RDY: J1.c5 (RDY), J2.c5 (RDY), J3.c5 (RDY), J4.c5 (RDY), J6.10
/R~W: J1.c29 (R~W), J2.c29 (R~W), J3.c29 (R~W), J4.c29 (R~W), J6.58
/SO: J1.c14 (SO), J2.c14 (SO), J3.c14 (SO), J4.c14 (SO), J6.28
/~80_SEL: J1.c11 (~80_SEL), J2.c11 (~80_SEL), J3.c11 (~80_SEL), J4.c11 (~80_SEL), J6.22
/~128K_SEL: J1.a6 (~128K_SEL), J2.a6 (~128K_SEL), J3.a6 (~128K_SEL), J4.a6 (~128K_SEL), J6.11
/~A0_SEL: J1.a11 (~A0_SEL), J2.a11 (~A0_SEL), J3.a11 (~A0_SEL), J4.a11 (~A0_SEL), J6.21
/~C0_SEL: J1.c6 (~C0_SEL), J2.c6 (~C0_SEL), J3.c6 (~C0_SEL), J4.c6 (~C0_SEL), J6.12
/~IRQ: J1.a12 (~IRQ), J2.a12 (~IRQ), J3.a12 (~IRQ), J4.a12 (~IRQ), J6.23
/~K2: J1.c28 (~K2), J2.c28 (~K2), J3.c28 (~K2), J4.c28 (~K2), J6.56
/~K3: J1.c18 (~K3), J2.c18 (~K3), J3.c18 (~K3), J4.c18 (~K3), J6.36
/~K4: J1.a17 (~K4), J2.a17 (~K4), J3.a17 (~K4), J4.a17 (~K4), J6.33
/~K5: J1.a15 (~K5), J2.a15 (~K5), J3.a15 (~K5), J4.a15 (~K5), J6.29
/~K6: J1.c15 (~K6), J2.c15 (~K6), J3.c15 (~K6), J4.c15 (~K6), J6.30
/~K7: J1.a14 (~K7), J2.a14 (~K7), J3.a14 (~K7), J4.a14 (~K7), J6.27
/~NMI: J1.c12 (~NMI), J2.c12 (~NMI), J3.c12 (~NMI), J4.c12 (~NMI), J6.24
/~RAM_SEL: J1.a29 (~RAM_SEL), J2.a29 (~RAM_SEL), J3.a29 (~RAM_SEL), J4.a29 (~RAM_SEL), J6.57
/~RES: J1.a5 (~RES), J2.a5 (~RES), J3.a5 (~RES), J4.a5 (~RES), J6.9
GND: C1.2 (-), C2.2 (-), C3.2 (-), D1.1 (K), D2.1 (K), D3.2 (A), J1.a4 (GND), J1.a32 (GND), J1.c4 (GND), J1.c32 (GND), J2.a4 (GND), J2.a32 (GND), J2.c4 (GND), J2.c32 (GND), J3.a4 (GND), J3.a32 (GND), J3.c4 (GND), J3.c32 (GND), J4.a4 (GND), J4.a32 (GND), J4.c4 (GND), J4.c32 (GND), J5.5, J5.6, J5.7, J5.8, J6.7, J6.8, J6.63, J6.64
unnamed: D1.2 (A), R1.2
unnamed: D2.2 (A), R2.2
unnamed: D3.1 (K), R3.2

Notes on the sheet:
Slot 2
Slot 4
Slot 1
Slot 3
